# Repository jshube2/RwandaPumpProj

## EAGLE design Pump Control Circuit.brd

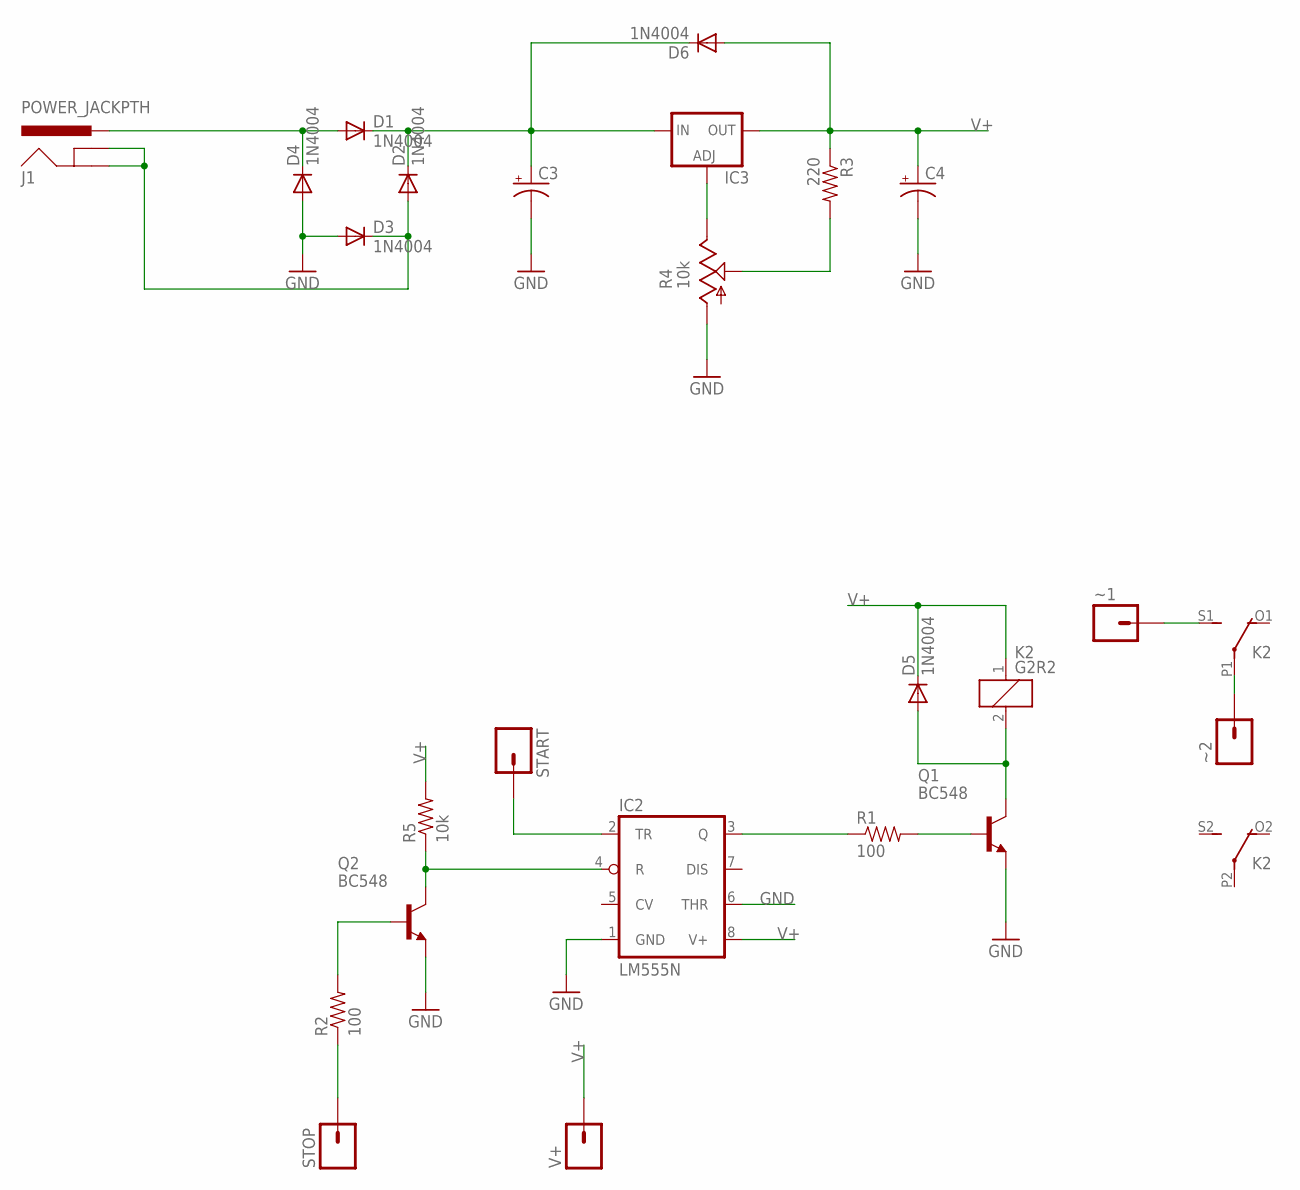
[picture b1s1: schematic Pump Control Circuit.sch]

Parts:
C3: CAP_POLPTH1; CPOL-RADIAL-100UF-25V
C4: CAP_POLPTH4; CPOL-RADIAL-1000UF-25V
D1, D2, D3, D4, D5, D6: 1N4004; DO41-10
IC2: LM555N; DIL08
IC3: LM317TS; 317TS
J1: POWER_JACKPTH; POWER_JACK_PTH
K2: G2R2
Q1, Q2: BC548; TO92-EBC
R1, R2: 100; AXIAL-0.3
R3: 220; AXIAL-0.3
R4: 10k; B64Y
R5: 10k; AXIAL-0.3
START: M01PTH; 1X01
STOP: M01PTH; 1X01
V+: M01PTH; 1X01
~1, ~2: M01PTH; 1X01

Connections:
GND: C3.2 (-), C4.-, D3.A, D4.A, IC2.1 (GND), IC2.6 (THR), Q1.E, Q2.E, R4.A
unnamed: IC3.1 (ADJ), R4.E
unnamed: Q2.B, R2.P$2 (2)
unnamed: D1.A, D4.C, J1.PWR
unnamed: IC2.4 (R), Q2.C, R5.P$1 (1)
unnamed: IC2.2 (TR), START.1
unnamed: R3.P$2 (2), R4.S
unnamed: K2.S1 (S), ~1.1
unnamed: C3.1 (+), D1.C, D2.C, D6.C, IC3.3 (IN)
unnamed: K2.P1, ~2.1
unnamed: Q1.B, R1.P$2 (2)
unnamed: D5.A, K2.2, Q1.C
unnamed: IC2.3 (Q), R1.P$1 (1)
unnamed: R2.P$1 (1), STOP.1
NEUTRAL: D2.A, D3.C, J1.GND, J1.GNDBREAK
V+: C4.+, D5.C, D6.A, IC2.8 (V+), IC3.2 (OUT), K2.1, R3.P$1 (1), R5.P$2 (2), V+.1

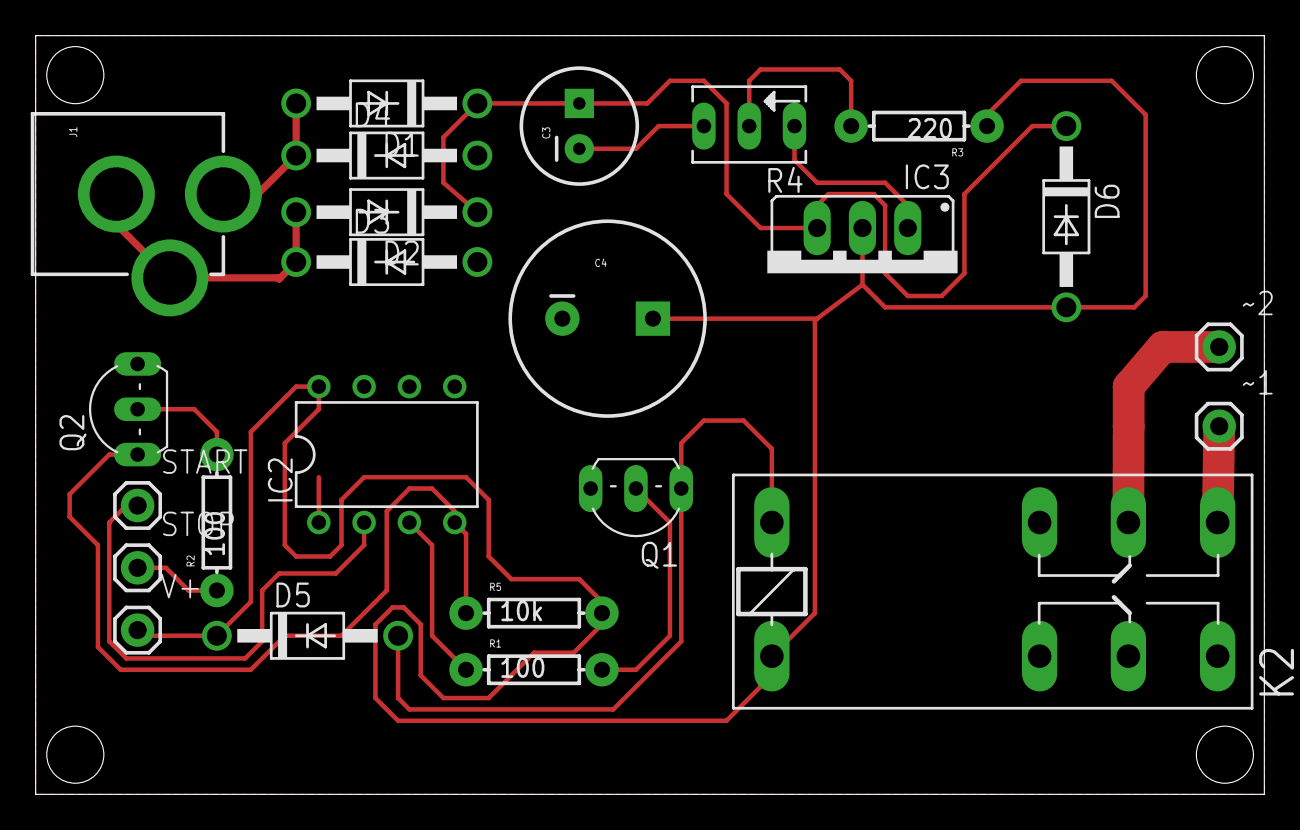
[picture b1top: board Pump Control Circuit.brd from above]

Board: 2 copper layers, 68.9 x 42.5 mm, 24 parts (0 on the bottom side), 16 nets.

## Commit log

2016-08-10 Add files via upload
    First iteration of the pump control circuit I implemented at Gihundwe Hospital in Kamembe, Rwanda
2016-08-10 Add files via upload
    I changed the relay on the board schematic to allow for more options and to also allow for relay sizes I believe to be more commonly available in Rwanda.
2016-08-11 Add files via upload
    Added a screen shot
2016-08-11 Add files via upload
    Fixed the voltage regulator footprint to not be intersecting with the relay footprint

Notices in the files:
parts and their libraries:
SparkFun-Capacitors: Licensing: Creative Commons ShareAlike 4.0 International - https://creativecommons.org/licenses/by-sa/4.0
